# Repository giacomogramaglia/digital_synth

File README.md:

# digital_synth
FPGA-based digital audio synthesizer board

Contains
- Schematics
- FPGA RTL files / Quartus II project
- KiCad project
- PCB production files

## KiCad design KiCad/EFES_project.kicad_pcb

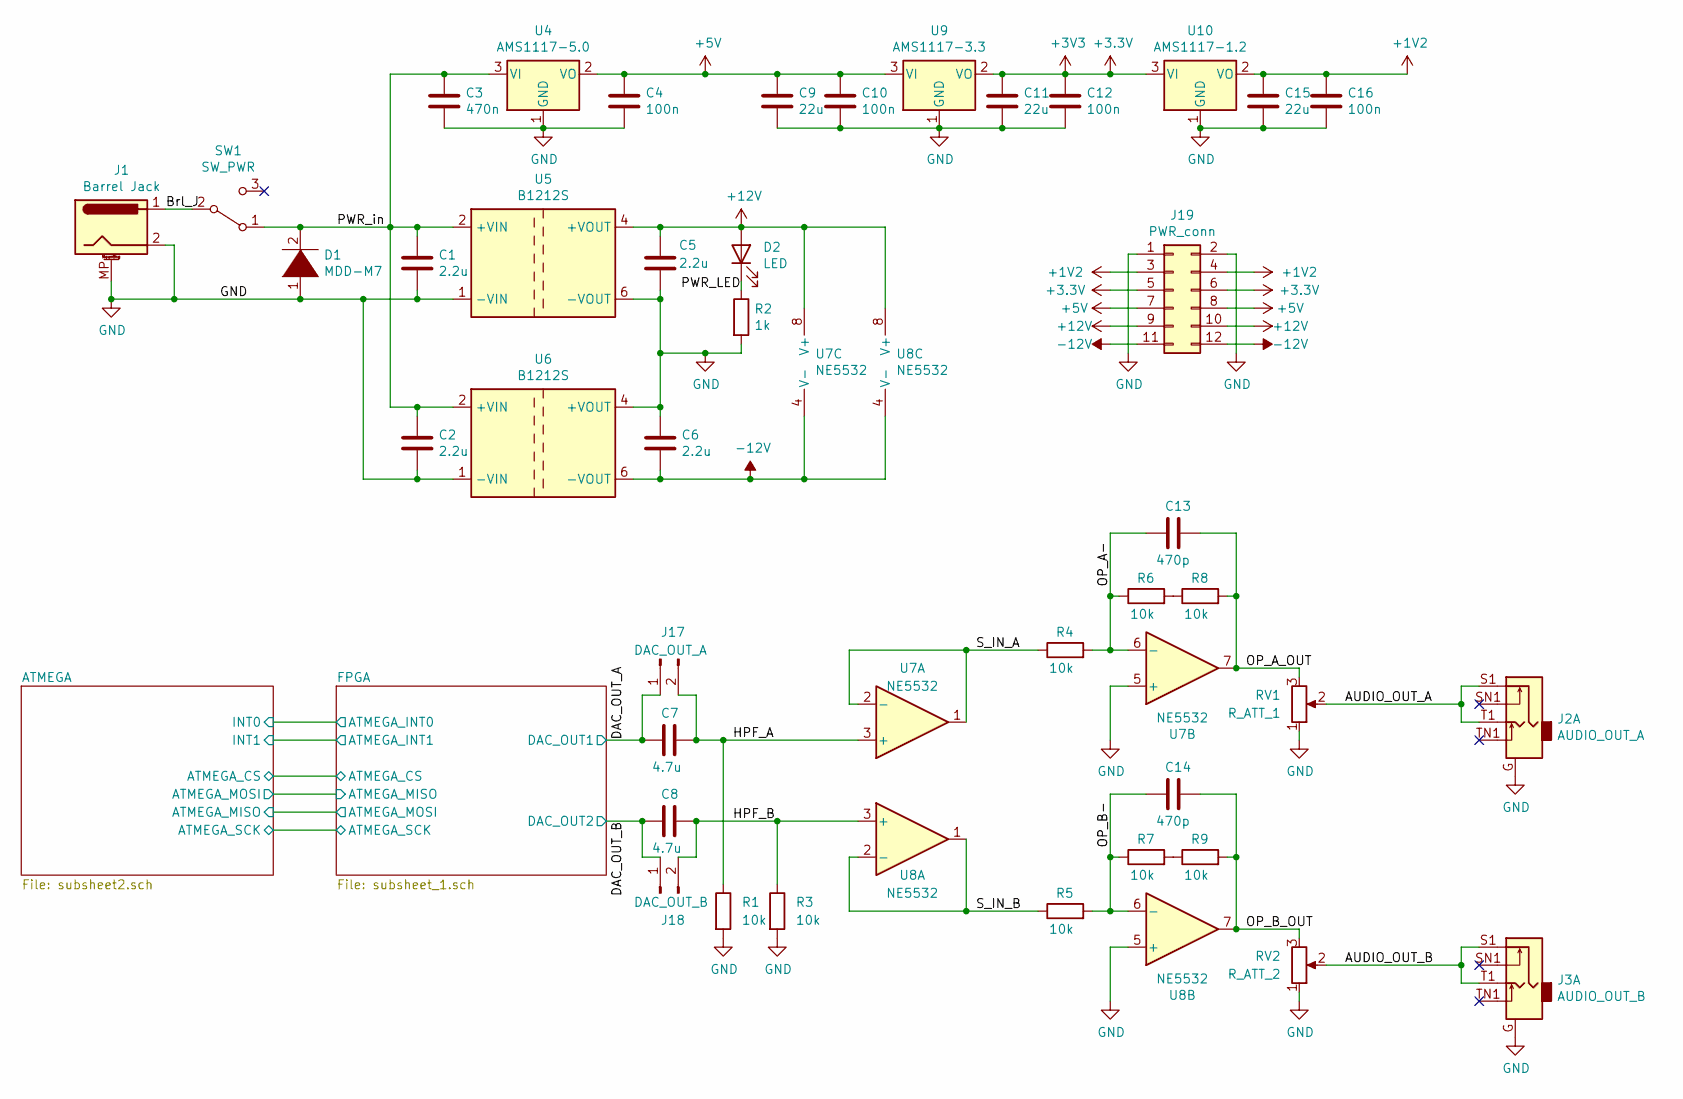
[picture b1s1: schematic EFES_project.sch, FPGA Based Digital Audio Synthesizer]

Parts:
C1, C2, C5, C6: 2.2u; C_0805_2012Metric
C3: 470n; C_0603_1608Metric
C4, C10, C12, C16: 100n; C_0402_1005Metric
C7, C8: 4.7u; C_0805_2012Metric
C9, C11, C15: 22u; C_0805_2012Metric
C13, C14: 470p; C_0805_2012Metric
D1: MDD-M7; D_SMA
D2: LED; LED_0805_2012Metric
J1: Barrel Jack; BarrelJack_Horizontal
J2: AUDIO_OUT_A; PJ-307
J3: AUDIO_OUT_B; PJ-307
J17: DAC_OUT_A; PinHeader_1x02_P2.54mm_Vertical
J18: DAC_OUT_B; PinHeader_1x02_P2.54mm_Vertical
J19: PWR_conn; PinHeader_2x06_P2.54mm_Vertical
R1, R3, R4, R5, R6, R7, R8, R9: 10k; R_0402_1005Metric
R2: 1k; R_1206_3216Metric
RV1: R_ATT_1; Potentiometer_Alpha_RD901F-40-00D_Single_Vertical
RV2: R_ATT_2; Potentiometer_Alpha_RD901F-40-00D_Single_Vertical
SW1: SW_PWR; MTS-103
U4: AMS1117-5.0; SOT-223-3_TabPin2
U5, U6: B1212S; Converter_DCDC_muRata_CRE1xxxxxxSC_THT
U7: NE5532; SOIC-8-1EP_3.9x4.9mm_P1.27mm_EP2.29x3mm
U8: NE5532
U9: AMS1117-3.3; SOT-223-3_TabPin2
U10: AMS1117-1.2; SOT-223-3_TabPin2

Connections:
+1V2: C15.1, C16.1, J19.3, J19.4, U10.2 (VO); also elsewhere on the board
+3V3: C11.1, C12.1, J19.5, J19.6, U9.2 (VO), U10.3 (VI); also elsewhere on the board
+5V: C4.1, C9.1, C10.1, J19.7, J19.8, U4.2 (VO), U9.3 (VI); also elsewhere on the board
-12V: C6.2, J19.11, J19.12, U6.3, U6.6 (-VOUT), U7.4 (V-), U8.4 (V-)
/AUDIO_OUT_A: J2.2, J2.3, J2.4, J2.5, J2.S1, J2.T1, RV1.2
/AUDIO_OUT_B: J3.2, J3.3, J3.4, J3.5, J3.S1, J3.T1, RV2.2
/Brl_J: J1.1, SW1.2 (B)
/DAC_OUT_A: C7.2, J17.1; also elsewhere on the board
/DAC_OUT_B: C8.2, J18.1; also elsewhere on the board
/HPF_A: C7.1, J17.2, R1.1, U7.3 (+)
/HPF_B: C8.1, J18.2, R3.1, U8.3 (+)
/OP_A-: C13.2, R4.2, R6.1, U7.6 (-)
/OP_A_OUT: C13.1, R8.2, RV1.3, U7.7
/OP_B-: C14.2, R5.2, R7.1, U8.6 (-)
/OP_B_OUT: C14.1, R9.2, RV2.3, U8.7
/PWR_LED: D2.1 (K), R2.1
/S_IN_A: R4.1, U7.1, U7.2 (-)
/S_IN_B: R5.1, U8.1, U8.2 (-)
GND: C1.2, C2.2, C3.2, C4.2, C5.2, C6.1, C9.2, C10.2, C11.2, C12.2, C15.2, C16.2, D1.1 (K), J1.2, J1.MP (MountPin), J2.1, J2.G, J3.1, J3.G, J19.1, J19.2, R1.2, R2.2, R3.2, RV1.1, RV2.1, U4.1 (GND), U5.1 (-VIN), U5.3, U5.6 (-VOUT), U6.1 (-VIN), U6.4 (+VOUT), U7.5 (+), U8.5 (+), U9.1 (GND), U10.1 (GND); also elsewhere on the board
unnamed: R6.2, R8.1
unnamed: R7.2, R9.1

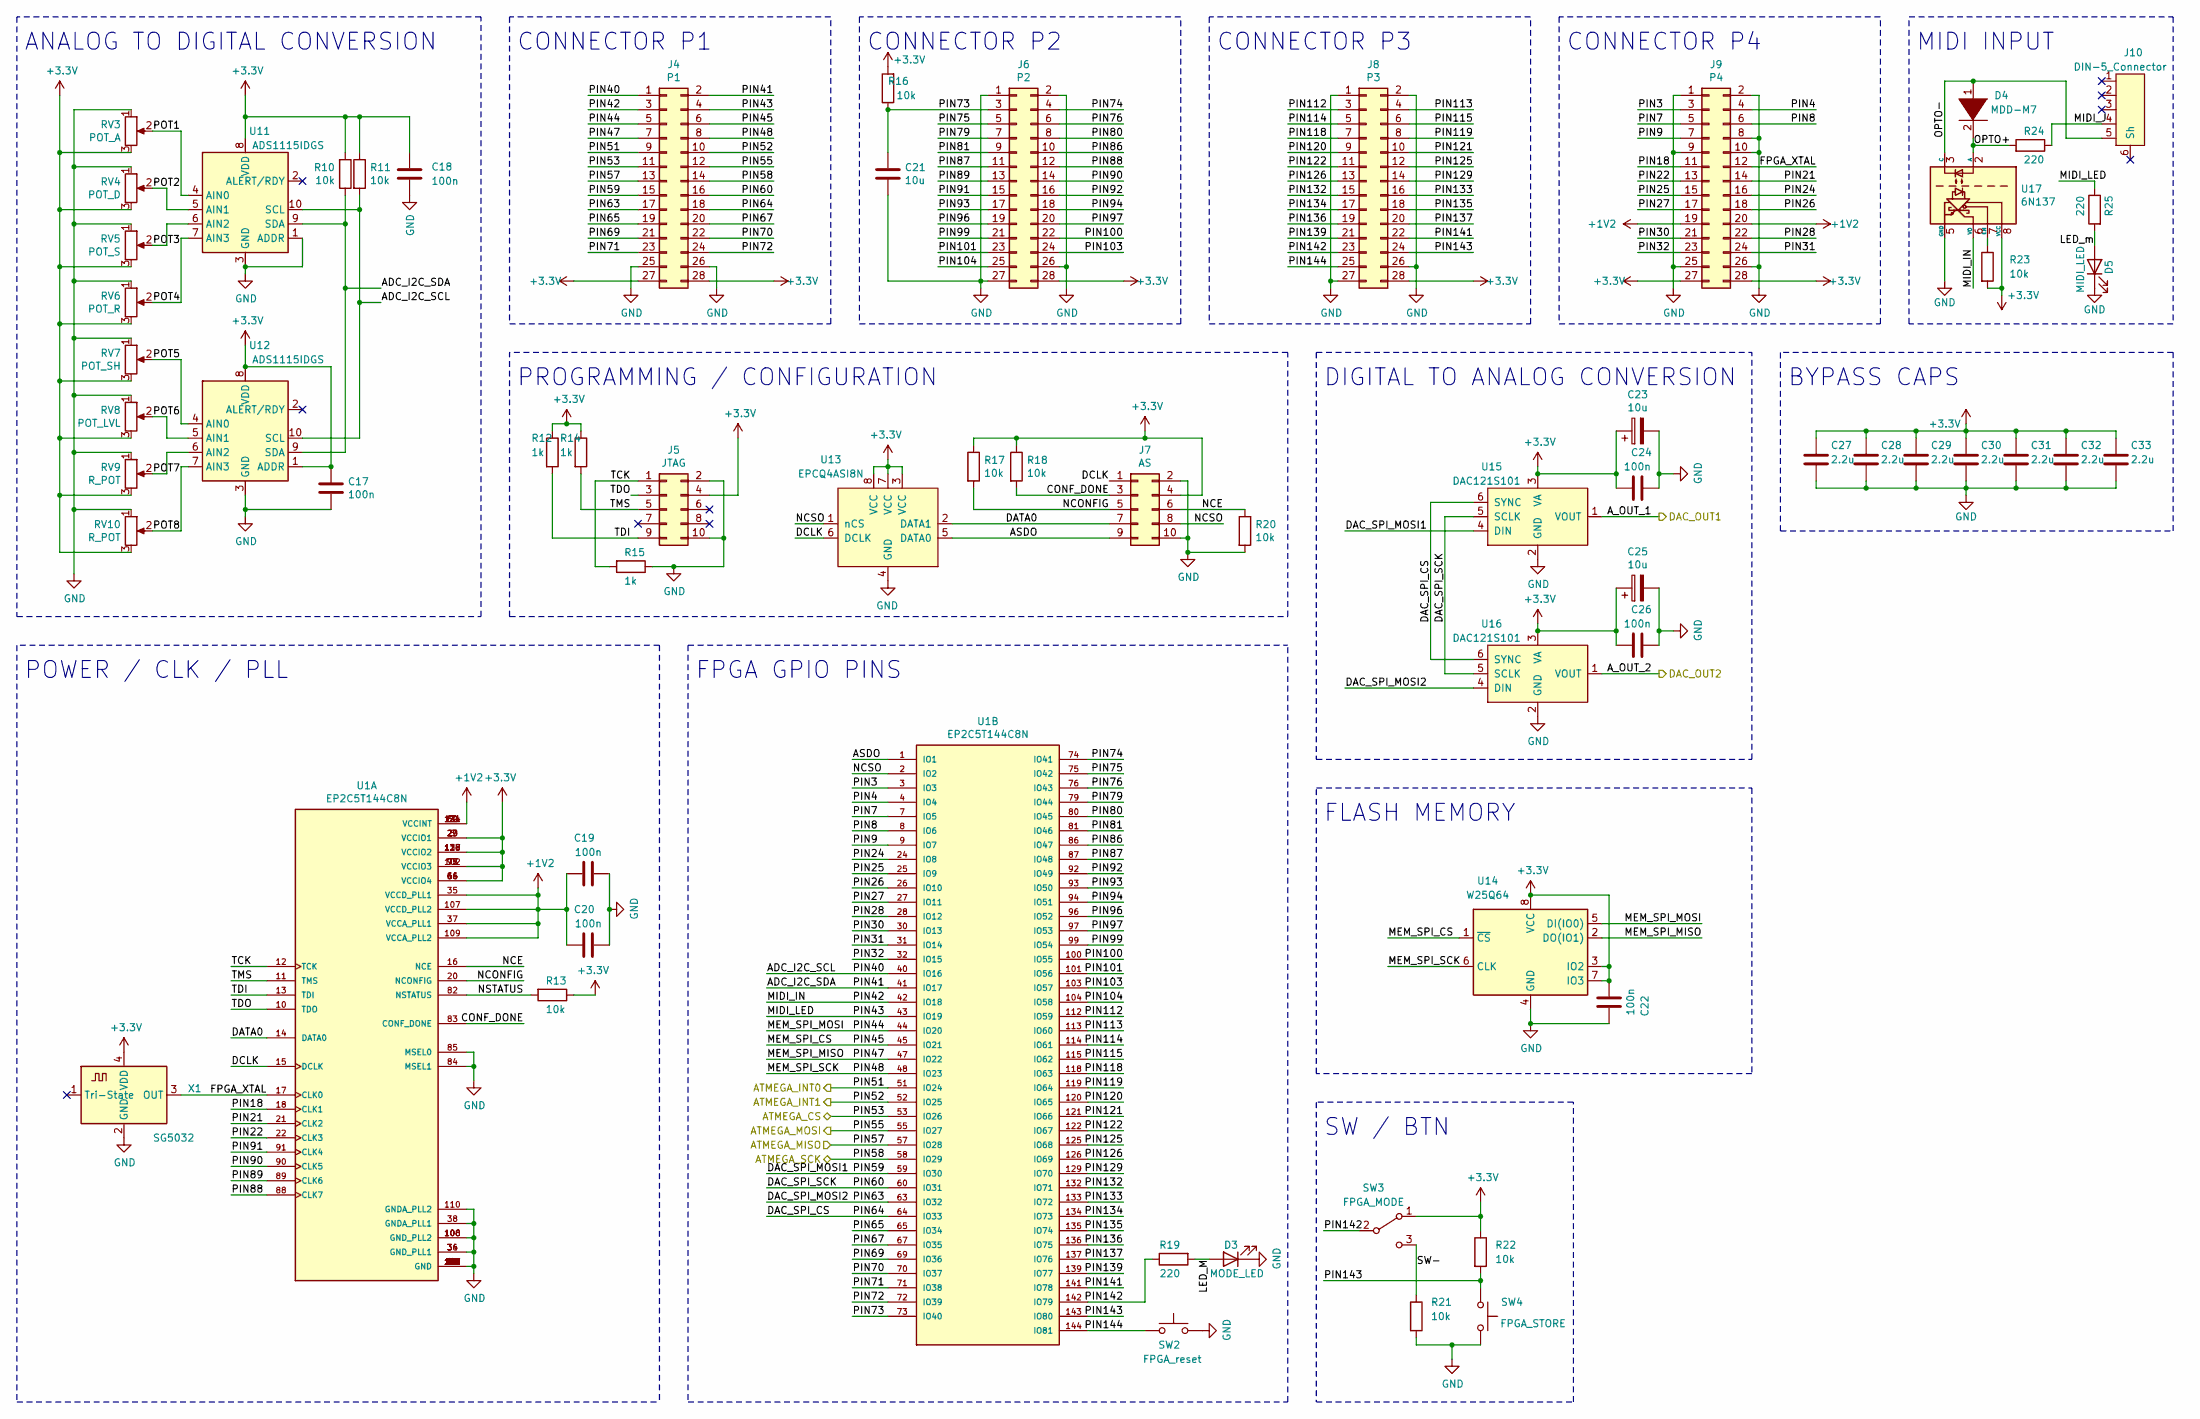
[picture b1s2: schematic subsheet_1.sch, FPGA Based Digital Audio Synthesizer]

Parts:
C17, C18, C19, C20, C22, C24, C26: 100n; C_0402_1005Metric
C21: 10u; C_1206_3216Metric
C23, C25: 10u; CP_EIA-3216-18_Kemet-A
C27, C28, C29, C30, C31, C32, C33: 2.2u; C_0805_2012Metric
D3: MODE_LED; LED_0805_2012Metric
D4: MDD-M7; D_SMA
D5: MIDI_LED; LED_0805_2012Metric
J4: P1; PinHeader_2x14_P2.54mm_Vertical
J5: JTAG; IDC-Header_2x05_P2.54mm_Vertical
J6: P2; PinHeader_2x14_P2.54mm_Vertical
J7: AS; IDC-Header_2x05_P2.54mm_Vertical
J8: P3; PinHeader_2x14_P2.54mm_Vertical
J9: P4; PinHeader_2x14_P2.54mm_Vertical
J10: DIN-5_Connector; DIN-504-M10
R10, R11, R13, R16, R17, R18, R20, R21, R22, R23: 10k; R_0402_1005Metric
R12, R14, R15: 1k; R_0603_1608Metric
R19, R24, R25: 220; R_0805_2012Metric
RV3: POT_A; Potentiometer_Alpha_RD901F-40-00D_Single_Vertical
RV4: POT_D; Potentiometer_Alpha_RD901F-40-00D_Single_Vertical
RV5: POT_S; Potentiometer_Alpha_RD901F-40-00D_Single_Vertical
RV6: POT_R; Potentiometer_Alpha_RD901F-40-00D_Single_Vertical
RV7: POT_SH; Potentiometer_Alpha_RD901F-40-00D_Single_Vertical
RV8: POT_LVL; Potentiometer_Alpha_RD901F-40-00D_Single_Vertical
RV9, RV10: R_POT; Potentiometer_Alpha_RD901F-40-00D_Single_Vertical
SW2: FPGA_reset; SW_Push_1P1T_NO_6x6mm_H9.5mm
SW3: FPGA_MODE; MTS-103
SW4: FPGA_STORE; SW_Push_1P1T_NO_6x6mm_H9.5mm
U1: EP2C5T144C8N; QFP50P2200X2200X160-144N
U11, U12: ADS1115IDGS; TSSOP-10_3x3mm_P0.5mm
U13: EPCQ4ASI8N; SOIC-8_3.9x4.9mm_P1.27mm
U14: W25Q64; SOIC-8_5.23x5.23mm_P1.27mm
U15, U16: DAC121S101; SOT-23-6
U17: 6N137; SOP-8_6.62x9.15mm_P2.54mm
X1: SG5032; Crystal_SMD_5032-4Pin_5.0x3.2mm

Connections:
+1V2: C19.1, C20.1, J9.19, J9.20, U1.35 (VCCD_PLL1), U1.37 (VCCA_PLL1), U1.50 (VCCINT), U1.62 (VCCINT), U1.107 (VCCD_PLL2), U1.109 (VCCA_PLL2), U1.124 (VCCINT), U1.131 (VCCINT); also elsewhere on the board
+3V3: C17.1, C18.1, C22.2, C23.1, C24.2, C25.1, C26.2, C27.1, C28.1, C29.1, C30.1, C31.1, C32.1, C33.1, J4.27, J4.28, J5.4, J6.28, J7.4, J8.28, J9.27, J9.28, R10.2, R11.1, R12.1, R13.1, R14.1, R16.2, R17.1, R18.1, R22.1, R23.2, RV3.3, RV4.3, RV5.3, RV6.3, RV7.3, RV8.3, RV9.3, RV10.3, SW3.1 (A), U1.5 (VCCIO1), U1.23 (VCCIO1), U1.29 (VCCIO1), U1.46 (VCCIO4), U1.54 (VCCIO4), U1.66 (VCCIO4), U1.77 (VCCIO3), U1.95 (VCCIO3), U1.102 (VCCIO3), U1.116 (VCCIO2), U1.127 (VCCIO2), U1.138 (VCCIO2), U11.8 (VDD), U12.1 (ADDR), U12.8 (VDD), U13.3 (VCC), U13.7 (VCC), U13.8 (VCC), U14.3 (IO2), U14.7 (IO3), U14.8 (VCC), U15.3 (VA), U16.3 (VA), U17.8 (VCC), X1.4 (VDD); also elsewhere on the board
/ATMEGA/ATMEGA_CS: J4.11, U1.53 (IO26); also elsewhere on the board
/ATMEGA/ATMEGA_MISO: J4.12, U1.55 (IO27); also elsewhere on the board
/ATMEGA/ATMEGA_SCK: J4.14, U1.58 (IO29); also elsewhere on the board
/DAC_OUT_A: U15.1 (VOUT); also elsewhere on the board
/DAC_OUT_B: U16.1 (VOUT); also elsewhere on the board
/FPGA/ADC_I2C_SCL: J4.1, R11.2, U1.40 (IO16), U11.10 (SCL), U12.10 (SCL)
/FPGA/ADC_I2C_SDA: J4.2, R10.1, U1.41 (IO17), U11.9 (SDA), U12.9 (SDA)
/FPGA/ASDO: J7.9, U1.1 (IO1), U13.5 (DATA0)
/FPGA/ATMEGA_INT0: J4.9, U1.51 (IO24); also elsewhere on the board
/FPGA/ATMEGA_INT1: J4.10, U1.52 (IO25); also elsewhere on the board
/FPGA/ATMEGA_MISO: J4.13, U1.57 (IO28); also elsewhere on the board
/FPGA/CONF_DONE: J7.3, R18.2, U1.83 (CONF_DONE)
/FPGA/DAC_SPI_CS: J4.18, U1.64 (IO33), U15.6 (SYNC), U16.6 (SYNC)
/FPGA/DAC_SPI_MOSI1: J4.15, U1.59 (IO30), U15.4 (DIN)
/FPGA/DAC_SPI_MOSI2: J4.17, U1.63 (IO32), U16.4 (DIN)
/FPGA/DAC_SPI_SCK: J4.16, U1.60 (IO31), U15.5 (SCLK), U16.5 (SCLK)
/FPGA/DATA0: J7.7, U1.14 (DATA0), U13.2 (DATA1)
/FPGA/DCLK: J7.1, U1.15 (DCLK), U13.6 (DCLK)
/FPGA/FPGA_XTAL: J9.12, U1.17 (CLK0), X1.3 (OUT)
/FPGA/LED_M: D3.2 (A), R19.2
/FPGA/LED_m: D5.2 (A), R25.2
/FPGA/MEM_SPI_CS: J4.6, U1.45 (IO21), U14.1 (~CS)
/FPGA/MEM_SPI_MISO: J4.7, U1.47 (IO22), U14.2 (DO(IO1))
/FPGA/MEM_SPI_MOSI: J4.5, U1.44 (IO20), U14.5 (DI(IO0))
/FPGA/MEM_SPI_SCK: J4.8, U1.48 (IO23), U14.6 (CLK)
/FPGA/MIDI_IN: J4.3, U1.42 (IO18), U17.6 (VO)
/FPGA/MIDI_J: J10.4, R24.1
/FPGA/MIDI_LED: J4.4, R25.1, U1.43 (IO19)
/FPGA/NCE: J7.6, R20.1, U1.16 (NCE)
/FPGA/NCONFIG: J7.5, R17.2, U1.20 (NCONFIG)
/FPGA/NCSO: J7.8, U1.2 (IO2), U13.1 (nCS)
/FPGA/NSTATUS: R13.2, U1.82 (NSTATUS)
/FPGA/OPTO+: D4.2 (A), R24.2, U17.2 (A)
/FPGA/OPTO-: D4.1 (K), J10.5, U17.3 (C)
/FPGA/PIN3: J9.3, U1.3 (IO3)
/FPGA/PIN4: J9.4, U1.4 (IO4)
/FPGA/PIN7: J9.5, U1.7 (IO5)
/FPGA/PIN8: J9.6, U1.8 (IO6)
/FPGA/PIN9: J9.7, U1.9 (IO7)
/FPGA/PIN18: J9.11, U1.18 (CLK1)
/FPGA/PIN21: J9.14, U1.21 (CLK2)
/FPGA/PIN22: J9.13, U1.22 (CLK3)
/FPGA/PIN24: J9.16, U1.24 (IO8)
/FPGA/PIN25: J9.15, U1.25 (IO9)
/FPGA/PIN26: J9.18, U1.26 (IO10)
/FPGA/PIN27: J9.17, U1.27 (IO11)
/FPGA/PIN28: J9.22, U1.28 (IO12)
/FPGA/PIN30: J9.21, U1.30 (IO13)
/FPGA/PIN31: J9.24, U1.31 (IO14)
/FPGA/PIN32: J9.23, U1.32 (IO15)
/FPGA/PIN65: J4.19, U1.65 (IO34)
/FPGA/PIN67: J4.20, U1.67 (IO35)
/FPGA/PIN69: J4.21, U1.69 (IO36)
/FPGA/PIN70: J4.22, U1.70 (IO37)
/FPGA/PIN71: J4.23, U1.71 (IO38)
/FPGA/PIN72: J4.24, U1.72 (IO39)
/FPGA/PIN73: C21.1, J6.3, R16.1, U1.73 (IO40)
/FPGA/PIN74: J6.4, U1.74 (IO41)
/FPGA/PIN75: J6.5, U1.75 (IO42)
/FPGA/PIN76: J6.6, U1.76 (IO43)
/FPGA/PIN79: J6.7, U1.79 (IO44)
/FPGA/PIN80: J6.8, U1.80 (IO45)
/FPGA/PIN81: J6.9, U1.81 (IO46)
/FPGA/PIN86: J6.10, U1.86 (IO47)
/FPGA/PIN87: J6.11, U1.87 (IO48)
/FPGA/PIN88: J6.12, U1.88 (CLK7)
/FPGA/PIN89: J6.13, U1.89 (CLK6)
/FPGA/PIN90: J6.14, U1.90 (CLK5)
/FPGA/PIN91: J6.15, U1.91 (CLK4)
/FPGA/PIN92: J6.16, U1.92 (IO49)
/FPGA/PIN93: J6.17, U1.93 (IO50)
/FPGA/PIN94: J6.18, U1.94 (IO51)
/FPGA/PIN96: J6.19, U1.96 (IO52)
/FPGA/PIN97: J6.20, U1.97 (IO53)
/FPGA/PIN99: J6.21, U1.99 (IO54)
/FPGA/PIN100: J6.22, U1.100 (IO55)
/FPGA/PIN101: J6.23, U1.101 (IO56)
/FPGA/PIN103: J6.24, U1.103 (IO57)
/FPGA/PIN104: J6.25, U1.104 (IO58)
/FPGA/PIN112: J8.3, U1.112 (IO59)
/FPGA/PIN113: J8.4, U1.113 (IO60)
/FPGA/PIN114: J8.5, U1.114 (IO61)
/FPGA/PIN115: J8.6, U1.115 (IO62)
/FPGA/PIN118: J8.7, U1.118 (IO63)
/FPGA/PIN119: J8.8, U1.119 (IO64)
/FPGA/PIN120: J8.9, U1.120 (IO65)
/FPGA/PIN121: J8.10, U1.121 (IO66)
/FPGA/PIN122: J8.11, U1.122 (IO67)
/FPGA/PIN125: J8.12, U1.125 (IO68)
/FPGA/PIN126: J8.13, U1.126 (IO69)
/FPGA/PIN129: J8.14, U1.129 (IO70)
/FPGA/PIN132: J8.15, U1.132 (IO71)
/FPGA/PIN133: J8.16, U1.133 (IO72)
/FPGA/PIN134: J8.17, U1.134 (IO73)
/FPGA/PIN135: J8.18, U1.135 (IO74)
/FPGA/PIN136: J8.19, U1.136 (IO75)
/FPGA/PIN137: J8.20, U1.137 (IO76)
/FPGA/PIN139: J8.21, U1.139 (IO77)
/FPGA/PIN141: J8.22, U1.141 (IO78)
/FPGA/PIN142: J8.23, R19.1, SW3.2 (B), U1.142 (IO79)
/FPGA/PIN143: J8.24, R22.2, SW4.1, U1.143 (IO80)
/FPGA/PIN144: J8.25, SW2.1, U1.144 (IO81)
/FPGA/POT1: RV3.2, U11.4 (AIN0)
/FPGA/POT2: RV4.2, U11.5 (AIN1)
/FPGA/POT3: RV5.2, U11.6 (AIN2)
/FPGA/POT4: RV6.2, U11.7 (AIN3)
/FPGA/POT5: RV7.2, U12.4 (AIN0)
/FPGA/POT6: RV8.2, U12.5 (AIN1)
/FPGA/POT7: RV9.2, U12.6 (AIN2)
/FPGA/POT8: RV10.2, U12.7 (AIN3)
/FPGA/SW-: R21.1, SW3.3 (C)
/FPGA/TCK: J5.1, R15.2, U1.12 (TCK)
/FPGA/TDI: J5.9, R12.2, U1.13 (TDI)
/FPGA/TDO: J5.3, U1.10 (TDO)
/FPGA/TMS: J5.5, R14.2, U1.11 (TMS)
GND: C17.2, C18.2, C19.2, C20.2, C21.2, C22.1, C23.2, C24.1, C25.2, C26.1, C27.2, C28.2, C29.2, C30.2, C31.2, C32.2, C33.2, D3.1 (K), D5.1 (K), J4.25, J4.26, J5.2, J5.10, J6.1, J6.2, J6.26, J6.27, J7.2, J7.10, J8.1, J8.2, J8.26, J8.27, J9.1, J9.2, J9.8, J9.9, J9.10, J9.25, J9.26, R15.1, R20.2, R21.2, RV3.1, RV4.1, RV5.1, RV6.1, RV7.1, RV8.1, RV9.1, RV10.1, SW2.2, SW4.2, U1.6 (GND), U1.19 (GND), U1.33 (GND), U1.34 (GND_PLL1), U1.36 (GND_PLL1), U1.38 (GNDA_PLL1), U1.39 (GND), U1.49 (GND), U1.56 (GND), U1.61 (GND), U1.68 (GND), U1.78 (GND), U1.84 (MSEL1), U1.85 (MSEL0), U1.98 (GND), U1.105 (GND), U1.106 (GND_PLL2), U1.108 (GND_PLL2), U1.110 (GNDA_PLL2), U1.111 (GND), U1.117 (GND), U1.123 (GND), U1.128 (GND), U1.130 (GND), U1.140 (GND), U11.1 (ADDR), U11.3 (GND), U12.3 (GND), U13.4 (GND), U14.4 (GND), U15.2 (GND), U16.2 (GND), U17.5 (GND), X1.2 (GND); also elsewhere on the board
unnamed: R23.1, U17.7 (EN)

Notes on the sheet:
ANALOG TO DIGITAL CONVERSION
PROGRAMMING / CONFIGURATION
POWER / CLK / PLL
CONNECTOR P4
CONNECTOR P3
CONNECTOR P2
CONNECTOR P1
FPGA GPIO PINS
DIGITAL TO ANALOG CONVERSION
FLASH MEMORY
MIDI INPUT
SW / BTN
BYPASS CAPS

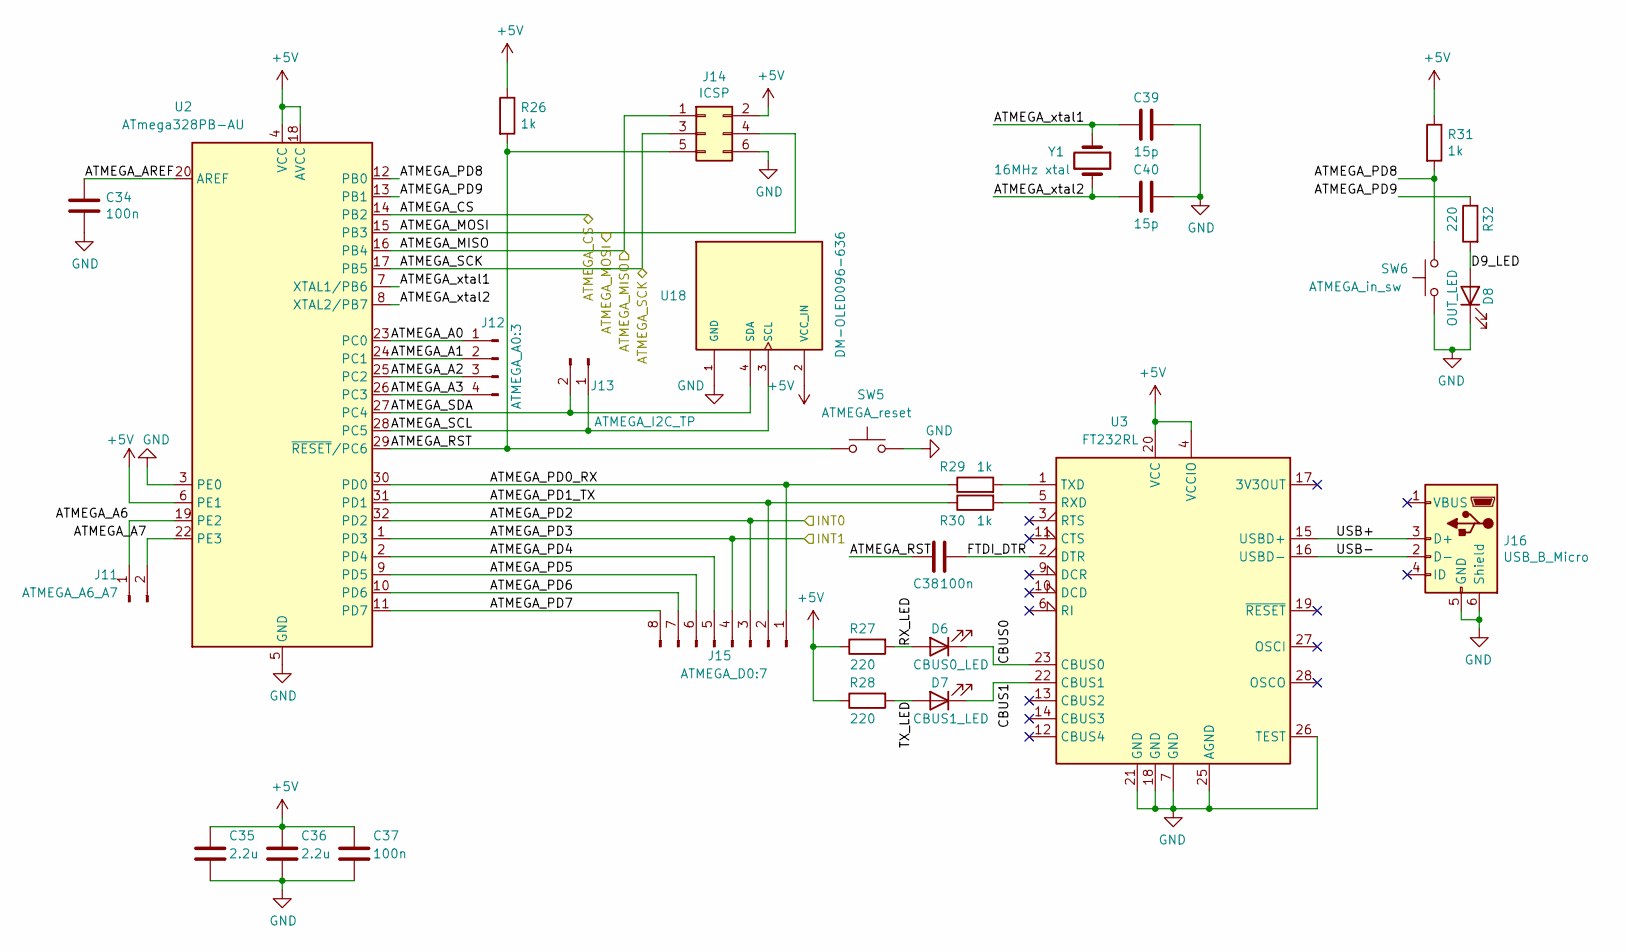
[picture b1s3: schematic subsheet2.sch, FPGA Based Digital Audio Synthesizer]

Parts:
C34, C37, C38: 100n; C_0402_1005Metric
C35, C36: 2.2u; C_0805_2012Metric
C39, C40: 15p; C_0603_1608Metric
D6: CBUS0_LED; LED_0805_2012Metric
D7: CBUS1_LED; LED_0805_2012Metric
D8: OUT_LED; LED_0805_2012Metric
J11: ATMEGA_A6_A7; PinHeader_1x02_P2.54mm_Vertical
J12: ATMEGA_A0:3; PinHeader_1x04_P2.54mm_Vertical
J13: ATMEGA_I2C_TP; PinHeader_1x02_P2.54mm_Vertical
J14: ICSP; PinHeader_2x03_P1.00mm_Vertical
J15: ATMEGA_D0:7; PinHeader_1x08_P2.54mm_Vertical
J16: USB_B_Micro; USB_Micro-B_Amphenol_10103594-0001LF_Horizontal
R26, R29, R30, R31: 1k; R_0603_1608Metric
R27, R28, R32: 220; R_0805_2012Metric
SW5: ATMEGA_reset; SW_Push_1P1T_NO_6x6mm_H9.5mm
SW6: ATMEGA_in_sw; SW_Push_1P1T_NO_6x6mm_H9.5mm
U2: ATmega328PB-AU; TQFP-32_7x7mm_P0.8mm
U3: FT232RL; SSOP-28_5.3x10.2mm_P0.65mm
U18: DM-OLED096-636; MODULE_DM-OLED096-636; PARTREV 2018-09-10
Y1: 16MHz xtal; Crystal_HC18-U_Vertical

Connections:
+5V: C35.1, C36.1, C37.1, J14.2, R26.1, R27.1, R28.1, R31.1, U2.4 (VCC), U2.6 (PE1), U2.18 (AVCC), U3.4 (VCCIO), U3.20 (VCC), U18.2 (VCC_IN); also elsewhere on the board
/ATMEGA/ATMEGA_A0: J12.1, U2.23 (PC0)
/ATMEGA/ATMEGA_A1: J12.2, U2.24 (PC1)
/ATMEGA/ATMEGA_A2: J12.3, U2.25 (PC2)
/ATMEGA/ATMEGA_A3: J12.4, U2.26 (PC3)
/ATMEGA/ATMEGA_A6: J11.1, U2.19 (PE2)
/ATMEGA/ATMEGA_A7: J11.2, U2.22 (PE3)
/ATMEGA/ATMEGA_AREF: C34.1, U2.20 (AREF)
/ATMEGA/ATMEGA_CS: U2.14 (PB2); also elsewhere on the board
/ATMEGA/ATMEGA_MISO: J14.1, U2.16 (PB4); also elsewhere on the board
/ATMEGA/ATMEGA_PD0_RX: J15.1, R29.1, U2.30 (PD0)
/ATMEGA/ATMEGA_PD1_TX: J15.2, R30.1, U2.31 (PD1)
/ATMEGA/ATMEGA_PD4: J15.5, U2.2 (PD4)
/ATMEGA/ATMEGA_PD5: J15.6, U2.9 (PD5)
/ATMEGA/ATMEGA_PD6: J15.7, U2.10 (PD6)
/ATMEGA/ATMEGA_PD7: J15.8, U2.11 (PD7)
/ATMEGA/ATMEGA_PD8: R31.2, SW6.2, U2.12 (PB0)
/ATMEGA/ATMEGA_PD9: R32.1, U2.13 (PB1)
/ATMEGA/ATMEGA_RST: C38.2, J14.5, R26.2, SW5.1, U2.29 (~RESET~/PC6)
/ATMEGA/ATMEGA_SCK: J14.3, U2.17 (PB5); also elsewhere on the board
/ATMEGA/ATMEGA_SCL: J13.1, U2.28 (PC5), U18.3 (SCL)
/ATMEGA/ATMEGA_SDA: J13.2, U2.27 (PC4), U18.4 (SDA)
/ATMEGA/ATMEGA_xtal1: C39.2, U2.7 (XTAL1/PB6), Y1.1
/ATMEGA/ATMEGA_xtal2: C40.2, U2.8 (XTAL2/PB7), Y1.2
/ATMEGA/CBUS0: D6.1 (K), U3.23 (CBUS0)
/ATMEGA/CBUS1: D7.1 (K), U3.22 (CBUS1)
/ATMEGA/D9_LED: D8.2 (A), R32.2
/ATMEGA/FTDI_DTR: C38.1, U3.2 (DTR)
/ATMEGA/RX_LED: D6.2 (A), R27.2
/ATMEGA/TX_LED: D7.2 (A), R28.2
/ATMEGA/USB+: J16.3 (D+), U3.15 (USBD+)
/ATMEGA/USB-: J16.2 (D-), U3.16 (USBD-)
/FPGA/ATMEGA_INT0: J15.3, U2.32 (PD2); also elsewhere on the board
/FPGA/ATMEGA_INT1: J15.4, U2.1 (PD3); also elsewhere on the board
/FPGA/ATMEGA_MISO: J14.4, U2.15 (PB3); also elsewhere on the board
GND: C34.2, C35.2, C36.2, C37.2, C39.1, C40.1, D8.1 (K), J14.6, J16.5 (GND), J16.6 (Shield), SW5.2, SW6.1, U2.3 (PE0), U2.5 (GND), U2.21 (GND), U3.7 (GND), U3.18 (GND), U3.21 (GND), U3.25 (AGND), U3.26 (TEST), U18.1 (GND); also elsewhere on the board
unnamed: R29.2, U3.1 (TXD)
unnamed: R30.2, U3.5 (RXD)

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
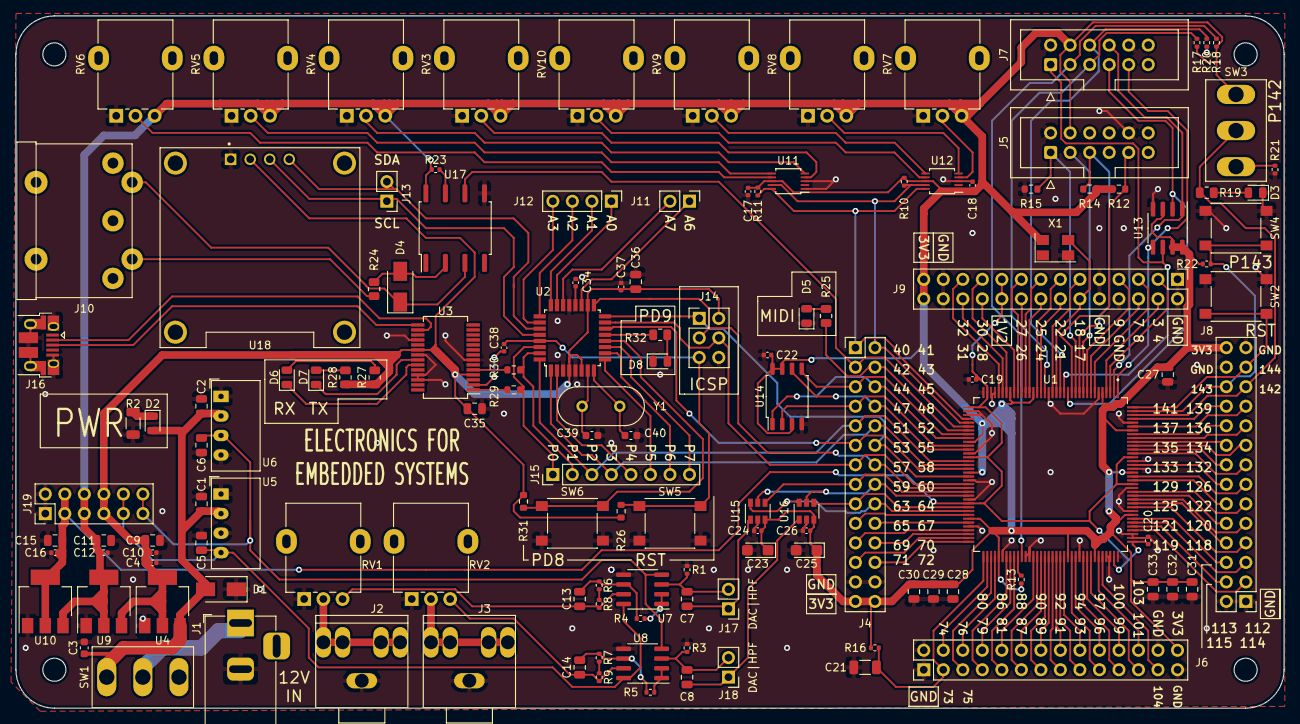
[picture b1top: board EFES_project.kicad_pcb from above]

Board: 2 copper layers, 165.0 x 90.1 mm, 135 parts (0 on the bottom side), 167 nets.

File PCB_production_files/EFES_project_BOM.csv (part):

Comment,Designator,Footprint,JLCPCB Part #?optional?,,,,,,,,,,,,,,,,,,,,,,,,,,,,,,,,
2.2u,C1,Capacitor_SMD:C_0805_2012Metric,Device:C,,,,,,,,,,,,,,,,,,,,,,,,,,,,,,,,
2.2u,C2,Capacitor_SMD:C_0805_2012Metric,Device:C,,,,,,,,,,,,,,,,,,,,,,,,,,,,,,,,
470n,C3,Capacitor_SMD:C_0603_1608Metric,Device:C,,,,,,,,,,,,,,,,,,,,,,,,,,,,,,,,
100n,C4,Capacitor_SMD:C_0402_1005Metric,Device:C,,,,,,,,,,,,,,,,,,,,,,,,,,,,,,,,
2.2u,C5,Capacitor_SMD:C_0805_2012Metric,Device:C,,,,,,,,,,,,,,,,,,,,,,,,,,,,,,,,
2.2u,C6,Capacitor_SMD:C_0805_2012Metric,Device:C,,,,,,,,,,,,,,,,,,,,,,,,,,,,,,,,
4.7u,C7,Capacitor_SMD:C_0805_2012Metric,Device:C,,,,,,,,,,,,,,,,,,,,,,,,,,,,,,,,
4.7u,C8,Capacitor_SMD:C_0805_2012Metric,Device:C,,,,,,,,,,,,,,,,,,,,,,,,,,,,,,,,
22u,C9,Capacitor_SMD:C_0805_2012Metric,Device:C,,,,,,,,,,,,,,,,,,,,,,,,,,,,,,,,
100n,C10,Capacitor_SMD:C_0402_1005Metric,Device:C,,,,,,,,,,,,,,,,,,,,,,,,,,,,,,,,
22u,C11,Capacitor_SMD:C_0805_2012Metric,Device:C,,,,,,,,,,,,,,,,,,,,,,,,,,,,,,,,
100n,C12,Capacitor_SMD:C_0402_1005Metric,Device:C,,,,,,,,,,,,,,,,,,,,,,,,,,,,,,,,
470p,C13,Capacitor_SMD:C_0805_2012Metric,Device:C,,,,,,,,,,,,,,,,,,,,,,,,,,,,,,,,
470p,C14,Capacitor_SMD:C_0805_2012Metric,Device:C,,,,,,,,,,,,,,,,,,,,,,,,,,,,,,,,
22u,C15,Capacitor_SMD:C_0805_2012Metric,Device:C,,,,,,,,,,,,,,,,,,,,,,,,,,,,,,,,
100n,C16,Capacitor_SMD:C_0402_1005Metric,Device:C,,,,,,,,,,,,,,,,,,,,,,,,,,,,,,,,
100n,C17,Capacitor_SMD:C_0402_1005Metric,Device:C,,,,,,,,,,,,,,,,,,,,,,,,,,,,,,,,
100n,C18,Capacitor_SMD:C_0402_1005Metric,Device:C,,,,,,,,,,,,,,,,,,,,,,,,,,,,,,,,
100n,C19,Capacitor_SMD:C_0402_1005Metric,Device:C,,,,,,,,,,,,,,,,,,,,,,,,,,,,,,,,
100n,C20,Capacitor_SMD:C_0402_1005Metric,Device:C,,,,,,,,,,,,,,,,,,,,,,,,,,,,,,,,
10u,C21,Capacitor_SMD:C_1206_3216Metric,Device:C,,,,,,,,,,,,,,,,,,,,,,,,,,,,,,,,
100n,C22,Capacitor_SMD:C_0402_1005Metric,Device:C,,,,,,,,,,,,,,,,,,,,,,,,,,,,,,,,
10u,C23,Capacitor_Tantalum_SMD:CP_EIA-3216-18_Kemet-A,Device:CP,,,,,,,,,,,,,,,,,,,,,,,,,,,,,,,,
100n,C24,Capacitor_SMD:C_0402_1005Metric,Device:C,,,,,,,,,,,,,,,,,,,,,,,,,,,,,,,,
10u,C25,Capacitor_Tantalum_SMD:CP_EIA-3216-18_Kemet-A,Device:CP,,,,,,,,,,,,,,,,,,,,,,,,,,,,,,,,
100n,C26,Capacitor_SMD:C_0402_1005Metric,Device:C,,,,,,,,,,,,,,,,,,,,,,,,,,,,,,,,
2.2u,C27,Capacitor_SMD:C_0805_2012Metric,Device:C,,,,,,,,,,,,,,,,,,,,,,,,,,,,,,,,
2.2u,C28,Capacitor_SMD:C_0805_2012Metric,Device:C,,,,,,,,,,,,,,,,,,,,,,,,,,,,,,,,
2.2u,C29,Capacitor_SMD:C_0805_2012Metric,Device:C,,,,,,,,,,,,,,,,,,,,,,,,,,,,,,,,
2.2u,C30,Capacitor_SMD:C_0805_2012Metric,Device:C,,,,,,,,,,,,,,,,,,,,,,,,,,,,,,,,
2.2u,C31,Capacitor_SMD:C_0805_2012Metric,Device:C,,,,,,,,,,,,,,,,,,,,,,,,,,,,,,,,
2.2u,C32,Capacitor_SMD:C_0805_2012Metric,Device:C,,,,,,,,,,,,,,,,,,,,,,,,,,,,,,,,
2.2u,C33,Capacitor_SMD:C_0805_2012Metric,Device:C,,,,,,,,,,,,,,,,,,,,,,,,,,,,,,,,
100n,C34,Capacitor_SMD:C_0402_1005Metric,Device:C,,,,,,,,,,,,,,,,,,,,,,,,,,,,,,,,
2.2u,C35,Capacitor_SMD:C_0805_2012Metric,Device:C,,,,,,,,,,,,,,,,,,,,,,,,,,,,,,,,
2.2u,C36,Capacitor_SMD:C_0805_2012Metric,Device:C,,,,,,,,,,,,,,,,,,,,,,,,,,,,,,,,
100n,C37,Capacitor_SMD:C_0402_1005Metric,Device:C,,,,,,,,,,,,,,,,,,,,,,,,,,,,,,,,
100n,C38,Capacitor_SMD:C_0402_1005Metric,Device:C,,,,,,,,,,,,,,,,,,,,,,,,,,,,,,,,
15p,C39,Capacitor_SMD:C_0603_1608Metric,Device:C,,,,,,,,,,,,,,,,,,,,,,,,,,,,,,,,
15p,C40,Capacitor_SMD:C_0603_1608Metric,Device:C,,,,,,,,,,,,,,,,,,,,,,,,,,,,,,,,
MDD-M7,D1,Diode_SMD:D_SMA,pspice:DIODE,,,,,,,,,,,,,,,,,,,,,,,,,,,,,,,,
LED,D2,LED_SMD:LED_0805_2012Metric,Device:LED,,,,,,,,,,,,,,,,,,,,,,,,,,,,,,,,
MODE_LED,D3,LED_SMD:LED_0805_2012Metric,Device:LED,,,,,,,,,,,,,,,,,,,,,,,,,,,,,,,,
MDD-M7,D4,Diode_SMD:D_SMA,pspice:DIODE,,,,,,,,,,,,,,,,,,,,,,,,,,,,,,,,
MIDI_LED,D5,LED_SMD:LED_0805_2012Metric,Device:LED,,,,,,,,,,,,,,,,,,,,,,,,,,,,,,,,
CBUS0_LED,D6,LED_SMD:LED_0805_2012Metric,Device:LED,,,,,,,,,,,,,,,,,,,,,,,,,,,,,,,,
CBUS1_LED,D7,LED_SMD:LED_0805_2012Metric,Device:LED,,,,,,,,,,,,,,,,,,,,,,,,,,,,,,,,
OUT_LED,D8,LED_SMD:LED_0805_2012Metric,Device:LED,,,,,,,,,,,,,,,,,,,,,,,,,,,,,,,,
Barrel Jack,J1,Connector_BarrelJack:BarrelJack_Horizontal,Connector:Barrel_Jack_MountingPin,,,,,,,,,,,,,,,,,,,,,,,,,,,,,,,,
AUDIO_OUT_A,J2,DM-OLED096-636:PJ-307,Connector:AudioJack2_Dual_Ground_Switch,,,,,,,,,,,,,,,,,,,,,,,,,,,,,,,,
AUDIO_OUT_B,J3,DM-OLED096-636:PJ-307,Connector:AudioJack2_Dual_Ground_Switch,,,,,,,,,,,,,,,,,,,,,,,,,,,,,,,,
P1,J4,Connector_PinHeader_2.54mm:PinHeader_2x14_P2.54mm_Vertical,Connector_Generic:Conn_02x14_Odd_Even,,,,,,,,,,,,,,,,,,,,,,,,,,,,,,,,
JTAG,J5,Connector_IDC:IDC-Header_2x06_P2.54mm_Vertical,Connector_Generic:Conn_02x05_Odd_Even,,,,,,,,,,,,,,,,,,,,,,,,,,,,,,,,
P2,J6,Connector_PinHeader_2.54mm:PinHeader_2x14_P2.54mm_Vertical,Connector_Generic:Conn_02x14_Odd_Even,,,,,,,,,,,,,,,,,,,,,,,,,,,,,,,,
AS,J7,Connector_IDC:IDC-Header_2x06_P2.54mm_Vertical,Connector_Generic:Conn_02x05_Odd_Even,,,,,,,,,,,,,,,,,,,,,,,,,,,,,,,,
P3,J8,Connector_PinHeader_2.54mm:PinHeader_2x14_P2.54mm_Vertical,Connector_Generic:Conn_02x14_Odd_Even,,,,,,,,,,,,,,,,,,,,,,,,,,,,,,,,
P4,J9,Connector_PinHeader_2.54mm:PinHeader_2x14_P2.54mm_Vertical,Connector_Generic:Conn_02x14_Odd_Even,,,,,,,,,,,,,,,,,,,,,,,,,,,,,,,,
DIN-5_Connector,J10,DM-OLED096-636:DIN-504-M10,DAC121S101:DIN-5_Connector,,,,,,,,,,,,,,,,,,,,,,,,,,,,,,,,
ATMEGA_A6_A7,J11,Connector_PinHeader_2.54mm:PinHeader_1x02_P2.54mm_Vertical,Connector:Conn_01x02_Male,,,,,,,,,,,,,,,,,,,,,,,,,,,,,,,,
ATMEGA_A0:3,J12,Connector_PinHeader_2.54mm:PinHeader_1x04_P2.54mm_Vertical,Connector:Conn_01x04_Male,,,,,,,,,,,,,,,,,,,,,,,,,,,,,,,,
ATMEGA_I2C_TP,J13,Connector_PinHeader_2.54mm:PinHeader_1x02_P2.54mm_Vertical,Connector:Conn_01x02_Male,,,,,,,,,,,,,,,,,,,,,,,,,,,,,,,,
ICSP,J14,Connector_PinHeader_1.00mm:PinHeader_2x03_P1.00mm_Vertical,Connector_Generic:Conn_02x03_Odd_Even,,,,,,,,,,,,,,,,,,,,,,,,,,,,,,,,
ATMEGA_D0:7,J15,Connector_PinHeader_2.54mm:PinHeader_1x08_P2.54mm_Vertical,Connector:Conn_01x08_Male,,,,,,,,,,,,,,,,,,,,,,,,,,,,,,,,
USB_B_Micro,J16,Connector_USB:USB_Micro-B_Amphenol_10103594-0001LF_Horizontal,Connector:USB_B_Micro,,,,,,,,,,,,,,,,,,,,,,,,,,,,,,,,
DAC_OUT_A,J17,Connector_PinHeader_2.54mm:PinHeader_1x02_P2.54mm_Vertical,Connector:Conn_01x02_Male,,,,,,,,,,,,,,,,,,,,,,,,,,,,,,,,
DAC_OUT_B,J18,Connector_PinHeader_2.54mm:PinHeader_1x02_P2.54mm_Vertical,Connector:Conn_01x02_Male,,,,,,,,,,,,,,,,,,,,,,,,,,,,,,,,
PWR_conn,J19,Connector_PinHeader_2.54mm:PinHeader_2x06_P2.54mm_Vertical,Connector_Generic:Conn_02x06_Odd_Even,,,,,,,,,,,,,,,,,,,,,,,,,,,,,,,,
10k,R1,Resistor_SMD:R_0402_1005Metric,Device:R,,,,,,,,,,,,,,,,,,,,,,,,,,,,,,,,
1k,R2,Resistor_SMD:R_1206_3216Metric,Device:R,,,,,,,,,,,,,,,,,,,,,,,,,,,,,,,,
10k,R3,Resistor_SMD:R_0402_1005Metric,Device:R,,,,,,,,,,,,,,,,,,,,,,,,,,,,,,,,
10k,R4,Resistor_SMD:R_0402_1005Metric,Device:R,,,,,,,,,,,,,,,,,,,,,,,,,,,,,,,,
10k,R5,Resistor_SMD:R_0402_1005Metric,Device:R,,,,,,,,,,,,,,,,,,,,,,,,,,,,,,,,
10k,R6,Resistor_SMD:R_0402_1005Metric,Device:R,,,,,,,,,,,,,,,,,,,,,,,,,,,,,,,,
10k,R7,Resistor_SMD:R_0402_1005Metric,Device:R,,,,,,,,,,,,,,,,,,,,,,,,,,,,,,,,
10k,R8,Resistor_SMD:R_0402_1005Metric,Device:R,,,,,,,,,,,,,,,,,,,,,,,,,,,,,,,,
10k,R9,Resistor_SMD:R_0402_1005Metric,Device:R,,,,,,,,,,,,,,,,,,,,,,,,,,,,,,,,
10k,R10,Resistor_SMD:R_0402_1005Metric,Device:R,,,,,,,,,,,,,,,,,,,,,,,,,,,,,,,,
10k,R11,Resistor_SMD:R_0402_1005Metric,Device:R,,,,,,,,,,,,,,,,,,,,,,,,,,,,,,,,
1k,R12,Resistor_SMD:R_0603_1608Metric,Device:R,,,,,,,,,,,,,,,,,,,,,,,,,,,,,,,,
10k,R13,Resistor_SMD:R_0402_1005Metric,Device:R,,,,,,,,,,,,,,,,,,,,,,,,,,,,,,,,
1k,R14,Resistor_SMD:R_0603_1608Metric,Device:R,,,,,,,,,,,,,,,,,,,,,,,,,,,,,,,,
1k,R15,Resistor_SMD:R_0603_1608Metric,Device:R,,,,,,,,,,,,,,,,,,,,,,,,,,,,,,,,
10k,R16,Resistor_SMD:R_0402_1005Metric,Device:R,,,,,,,,,,,,,,,,,,,,,,,,,,,,,,,,
10k,R17,Resistor_SMD:R_0402_1005Metric,Device:R,,,,,,,,,,,,,,,,,,,,,,,,,,,,,,,,
10k,R18,Resistor_SMD:R_0402_1005Metric,Device:R,,,,,,,,,,,,,,,,,,,,,,,,,,,,,,,,
220,R19,Resistor_SMD:R_0805_2012Metric,Device:R,,,,,,,,,,,,,,,,,,,,,,,,,,,,,,,,
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
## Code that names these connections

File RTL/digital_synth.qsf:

# -------------------------------------------------------------------------- #
#
# Copyright (C) 1991-2013 Altera Corporation
# Your use of Altera Corporation's design tools, logic functions 
# and other software and tools, and its AMPP partner logic 
# functions, and any output files from any of the foregoing 
# (including device programming or simulation files), and any 
# associated documentation or information are expressly subject 
# to the terms and conditions of the Altera Program License 
# Subscription Agreement, Altera MegaCore Function License 
# Agreement, or other applicable license agreement, including, 
# without limitation, that your use is for the sole purpose of 
# programming logic devices manufactured by Altera and sold by 
# Altera or its authorized distributors.  Please refer to the 
# applicable agreement for further details.
#
# -------------------------------------------------------------------------- #
#
# Quartus II 64-Bit
# Version 13.0.1 Build 232 06/12/2013 Service Pack 1 SJ Web Edition
# Date created = 13:27:40  October 22, 2024
#
# -------------------------------------------------------------------------- #
#
# Notes:
#
# 1) The default values for assignments are stored in the file:
#		digital_synth_assignment_defaults.qdf
#    If this file doesn't exist, see file:
#		assignment_defaults.qdf
#
# 2) Altera recommends that you do not modify this file. This
#    file is updated automatically by the Quartus II software
#    and any changes you make may be lost or overwritten.
#
# -------------------------------------------------------------------------- #


set_global_assignment -name FAMILY "Cyclone II"
set_global_assignment -name DEVICE EP2C5T144C8
set_global_assignment -name TOP_LEVEL_ENTITY system
set_global_assignment -name ORIGINAL_QUARTUS_VERSION "13.0 SP1"
set_global_assignment -name PROJECT_CREATION_TIME_DATE "13:27:40  OCTOBER 22, 2024"
set_global_assignment -name LAST_QUARTUS_VERSION "13.0 SP1"
set_global_assignment -name PROJECT_OUTPUT_DIRECTORY output_files
set_global_assignment -name MIN_CORE_JUNCTION_TEMP 0
set_global_assignment -name MAX_CORE_JUNCTION_TEMP 85
set_global_assignment -name DEVICE_FILTER_PACKAGE TQFP
set_global_assignment -name DEVICE_FILTER_PIN_COUNT 144
set_global_assignment -name POWER_PRESET_COOLING_SOLUTION "23 MM HEAT SINK WITH 200 LFPM AIRFLOW"
set_global_assignment -name POWER_BOARD_THERMAL_MODEL "NONE (CONSERVATIVE)"
set_global_assignment -name STRATIX_DEVICE_IO_STANDARD "3.3-V LVTTL"
set_global_assignment -name PARTITION_NETLIST_TYPE SOURCE -section_id Top
set_global_assignment -name PARTITION_FITTER_PRESERVATION_LEVEL PLACEMENT_AND_ROUTING -section_id Top
set_global_assignment -name PARTITION_COLOR 16764057 -section_id Top
set_location_assignment PIN_17 -to clk
set_location_assignment PIN_64 -to CS_DAC
set_location_assignment PIN_45 -to CS_FLASH
set_location_assignment PIN_40 -to I2C_SCL
set_location_assignment PIN_41 -to I2C_SDA
set_location_assignment PIN_47 -to MISO_FLASH
set_location_assignment PIN_59 -to MOSI_DAC_a
set_location_assignment PIN_63 -to MOSI_DAC_b
set_location_assignment PIN_44 -to MOSI_FLASH
set_location_assignment PIN_143 -to rst
set_location_assignment PIN_60 -to SPI_SCL_DAC
set_location_assignment PIN_48 -to SPI_SCL_FLASH
set_global_assignment -name VHDL_FILE spi_master.vhd
set_global_assignment -name VHDL_FILE spi_master_dual_mosi.vhd
set_global_assignment -name VHDL_FILE pmod_dac.vhd
set_global_assignment -name VHDL_FILE i2c_master.vhd
set_global_assignment -name VHDL_FILE i2c_controller.vhd
set_global_assignment -name VHDL_FILE Debounce.vhd
set_global_assignment -name VHDL_FILE clock_divider.vhd
set_global_assignment -name VHDL_FILE system.vhd
set_global_assignment -name VHDL_FILE spi_flash_controller.vhd
set_global_assignment -name VHDL_FILE MIDI_interface.vhd
set_location_assignment PIN_42 -to MIDI_in
set_global_assignment -name USE_CONFIGURATION_DEVICE ON
set_global_assignment -name RESERVE_ALL_UNUSED_PINS "AS INPUT TRI-STATED"
set_global_assignment -name VHDL_FILE waveforms.vhd
set_location_assignment PIN_43 -to MIDI_LED
set_location_assignment PIN_51 -to ATMEGA_int0
set_location_assignment PIN_52 -to ATMEGA_int1
set_location_assignment PIN_142 -to MODE_SW
set_location_assignment PIN_144 -to STORE_BTN
set_global_assignment -name RESERVE_ALL_UNUSED_PINS_NO_OUTPUT_GND "AS INPUT TRI-STATED"
set_global_assignment -name RTLV_GROUP_COMB_LOGIC_IN_CLOUD OFF
set_global_assignment -name VHDL_FILE ADSR_VCA.vhd
set_global_assignment -name VHDL_FILE iir_lowpass.vhd
set_global_assignment -name VHDL_FILE LFO.vhd
set_instance_assignment -name PARTITION_HIERARCHY root_partition -to | -section_id Top

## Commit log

2026-01-29 Update README to include project contents
